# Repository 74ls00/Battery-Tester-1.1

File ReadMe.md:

#### Анализатор батареек и аккумуляторов
----
Анализатор батареек и аккумуляторов разрабатывался по заказу одного из импортёров элементов питания и по мотивам статей для Ф-Центра. Задача — измерение ёмкости и оценка качества батареек в разных режимах разряда, с построением детального графика и сохранением всех полученных данных для демонстрации представителям завода-производителя.

Основные возможности стенда:

- общение с компьютером по USB, полностью программное управление;
- питание от шины USB;
- четыре независимых канала разряда с током 0…3 А каждый и шагом изменения тока 3 мА;
- режимы разряда постоянным током, постоянной мощностью (ток растёт по мере разряда) и на постоянное сопротивление (ток падает по мере разряда);
- режим разряда импульсным током с заданной скважностью;
- любые элементы питания с напряжением до 4,75 В, от батареек до литиевых аккумуляторов;
- 10-битные АЦП и ЦАП;
- индивидуальная калибровка каждого канала по току и напряжению;
- хранение калибровочных параметров в ПЗУ микроконтроллера;
- построение графика напряжения на элементах в реальном времени;
- установка допустимого уровня разряда элементов;
- автоматическое отключение разряженных элементов;
- светодиодная индикация состояния каждого элемента;
- сохранение всех полученных данных в формате CSV;
- автоматический расчёт ёмкости в ампер-часах и ватт-часах, а также внутреннего сопротивления элементов.

Программное обеспечение:

~~[Страница автора](http://olegart.ru/wordpress/batterytester/)~~

[Тема на коте](http://radiokot.ru/forum/viewtopic.php?f=11&t=135313)

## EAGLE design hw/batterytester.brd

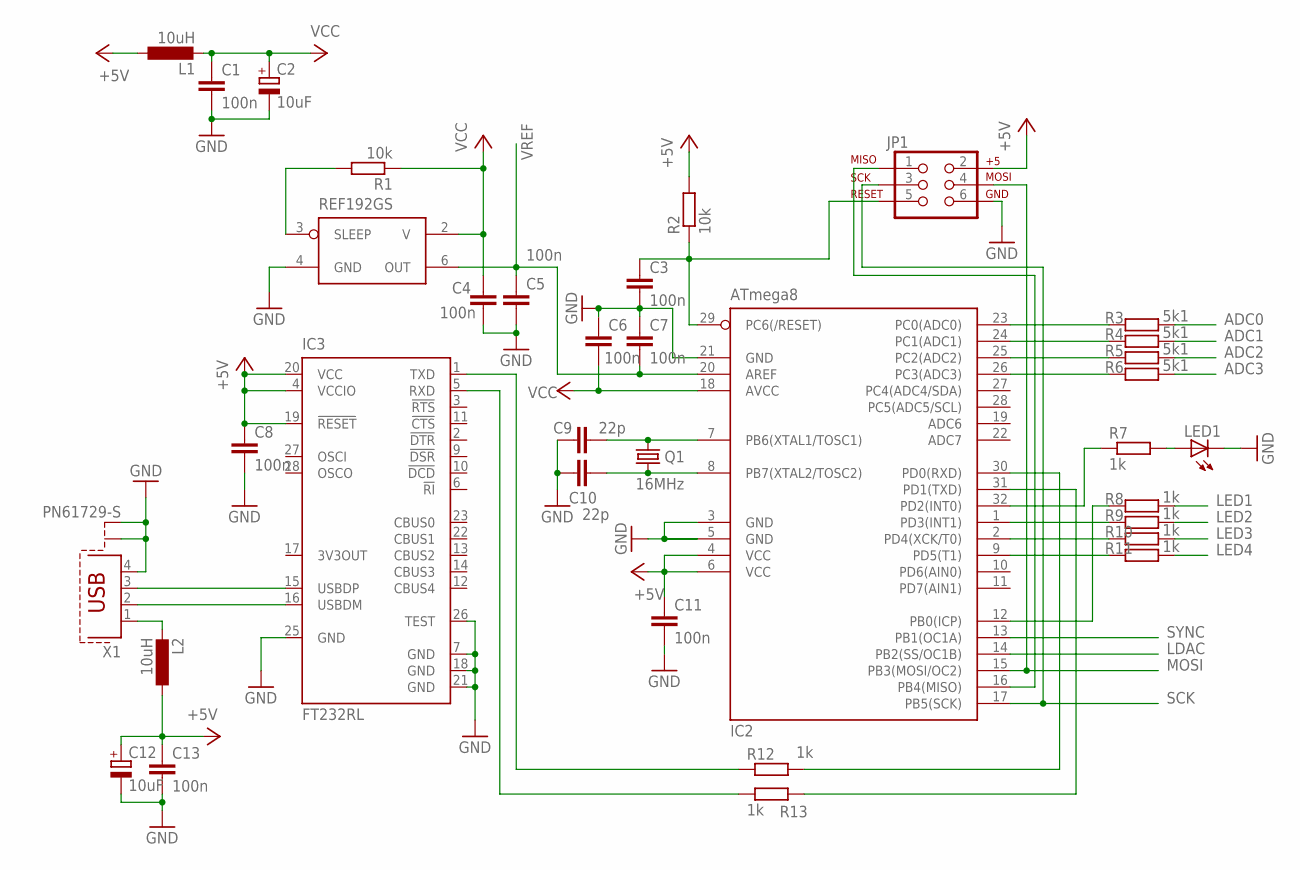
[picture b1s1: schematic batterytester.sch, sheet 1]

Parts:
C1, C3, C4, C5, C6, C7, C8, C11, C13: 100n; C0805
C2, C12: 10uF; SMC_B
C9, C10: 22p; C0805
IC1: REF192GS; SO8
IC2: ATmega8; TQFP32-08
IC3: FT232RL; SSOP28
JP1: AVR_SPI_PRG_6NS; 2X3-NS
L1, L2: 10uH; L1812
LED1: LED3MM
Q1: 16MHz; HC49/S
R1, R2: 10k; R0805
R3, R4, R5, R6: 5k1; R0805
R7, R8, R9, R10, R11, R12, R13: 1k; R0805
X1: PN61729-S

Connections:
+5V: C8.1, C11.1, C12.+, C13.1, IC2.4 (VCC), IC2.6 (VCC), IC3.4 (VCCIO), IC3.19 (!RESET), IC3.20 (VCC), JP1.2, L1.1, L2.1, R2.2; also elsewhere on the board
ADC0: R3.2; also elsewhere on the board
ADC1: R4.2; also elsewhere on the board
ADC2: R5.2; also elsewhere on the board
ADC3: R6.2; also elsewhere on the board
GND: C1.2, C2.-, C3.2, C4.2, C5.2, C6.1, C7.1, C8.2, C9.1, C10.1, C11.2, C12.-, C13.2, IC1.4 (GND), IC2.3 (GND), IC2.5 (GND), IC2.21 (GND), IC3.7 (GND), IC3.18 (GND), IC3.21 (GND), IC3.25 (GND), IC3.26 (TEST), JP1.6, LED1.K (C), X1.4, X1.S1, X1.S2; also elsewhere on the board
LDAC: IC2.14 (PB2(SS/OC1B)); also elsewhere on the board
LED1: R8.2; also elsewhere on the board
LED2: R9.2; also elsewhere on the board
LED3: R10.2; also elsewhere on the board
LED4: R11.2; also elsewhere on the board
MOSI: IC2.15 (PB3(MOSI/OC2)), JP1.4; also elsewhere on the board
unnamed: IC3.1 (TXD), R12.1
unnamed: IC3.5 (RXD), R13.1
unnamed: IC2.30 (PD0(RXD)), R12.2
unnamed: C9.2, IC2.7 (PB6(XTAL1/TOSC1)), Q1.1
unnamed: C10.2, IC2.8 (PB7(XTAL2/TOSC2)), Q1.2
unnamed: IC2.31 (PD1(TXD)), R13.2
unnamed: IC3.16 (USBDM), X1.2
unnamed: IC2.9 (PD5(T1)), R11.1
unnamed: C3.1, IC2.29 (PC6(/RESET)), JP1.5, R2.1
unnamed: IC2.2 (PD4(XCK/T0)), R10.1
unnamed: IC2.12 (PB0(ICP)), R8.1
unnamed: LED1.A, R7.2
unnamed: IC2.32 (PD2(INT0)), R7.1
unnamed: IC2.23 (PC0(ADC0)), R3.1
unnamed: IC3.15 (USBDP), X1.3
unnamed: L2.2, X1.1
unnamed: IC2.16 (PB4(MISO)), JP1.1
unnamed: IC1.3 (SLEEP), R1.2
unnamed: IC2.24 (PC1(ADC1)), R4.1
unnamed: IC2.25 (PC2(ADC2)), R5.1
unnamed: IC2.1 (PD3(INT1)), R9.1
unnamed: IC2.26 (PC3(ADC3)), R6.1
SCK: IC2.17 (PB5(SCK)), JP1.3; also elsewhere on the board
SYNC: IC2.13 (PB1(OC1A)); also elsewhere on the board
VCC: C1.1, C2.+, C4.1, C6.2, IC1.2 (V), IC2.18 (AVCC), L1.2, R1.1; also elsewhere on the board
VREF: C5.1, C7.2, IC1.6 (OUT), IC2.20 (AREF); also elsewhere on the board

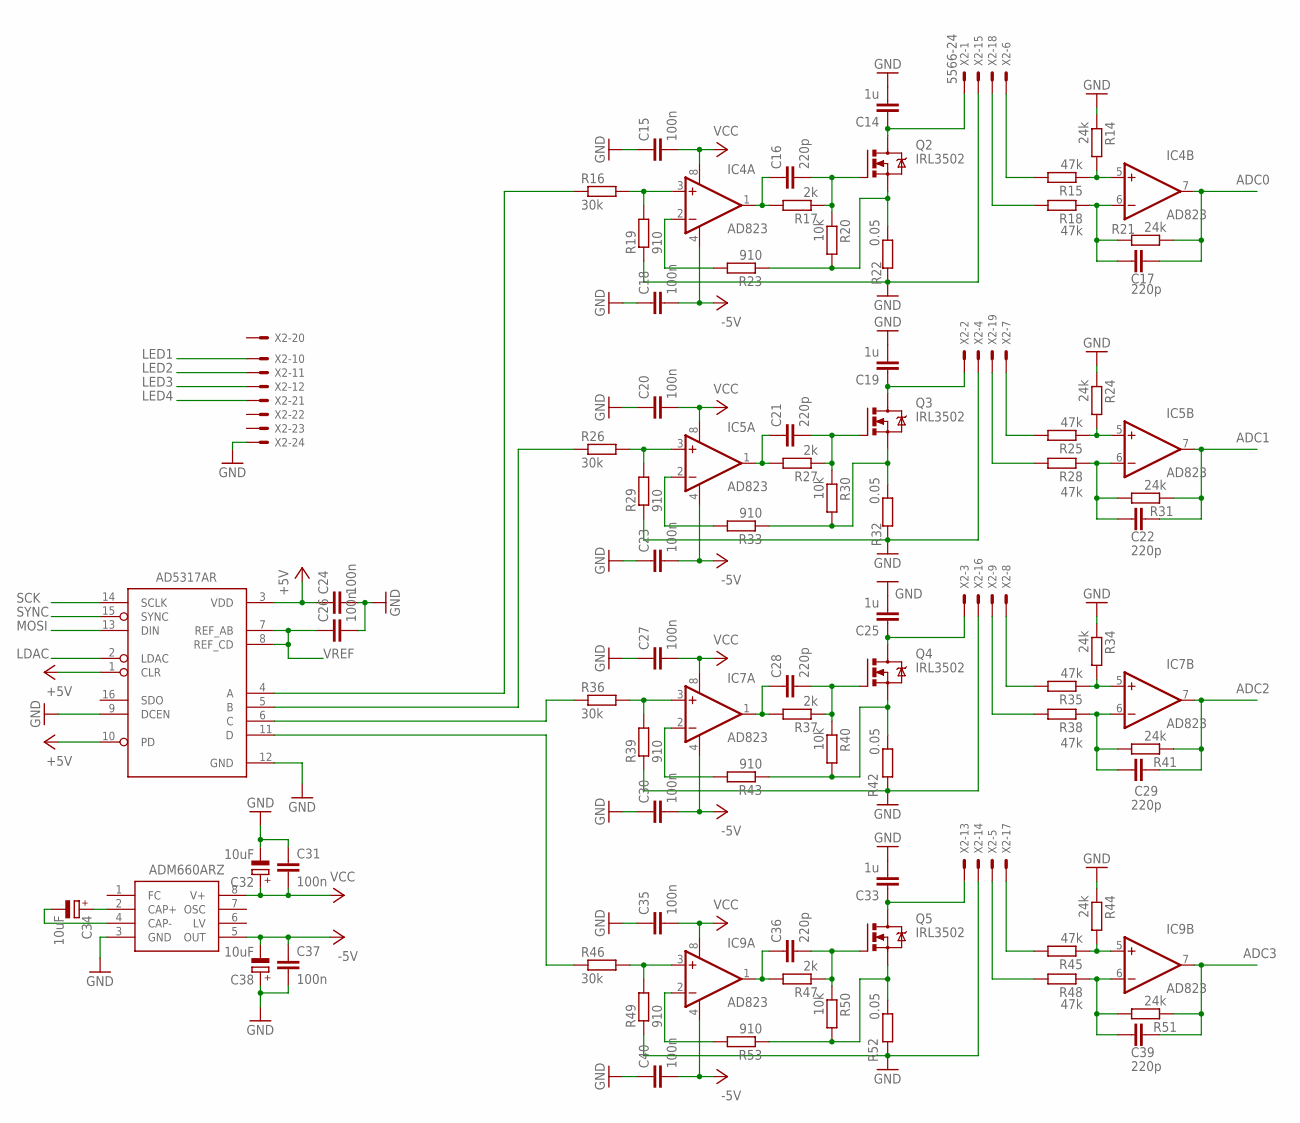
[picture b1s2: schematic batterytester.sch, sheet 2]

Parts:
C14, C19, C25, C33: 1u; C0805
C15, C18, C20, C23, C24, C26, C27, C30, C31, C35, C37, C40: 100n; C0805
C16, C17, C21, C22, C28, C29, C36, C39: 220p; C0805
C32, C34, C38: 10uF; SMC_B
IC4, IC5, IC7, IC9: AD823; SO8
IC6: AD5317AR; TSSOP16
IC8: ADM660ARZ; SO8
Q2, Q3, Q4, Q5: IRL3502; TO220BV
R14, R21, R24, R31, R34, R41, R44, R51: 24k; R0805
R15, R18, R25, R28, R35, R38, R45, R48: 47k; R0805
R16, R26, R36, R46: 30k; R0805
R17, R27, R37, R47: 2k; R0805
R19, R23, R29, R33, R39, R43, R49, R53: 910; R0805
R20, R30, R40, R50: 10k; R0805
R22, R32, R42, R52: 0.05; R2512
X2: 5566-24; 5569-24

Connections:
+5V: C24.1, IC6.1 (CLR), IC6.3 (VDD), IC6.10 (PD); also elsewhere on the board
-5V: C18.2, C23.2, C30.2, C37.1, C38.-, C40.2, IC4.4 (V-), IC5.4 (V-), IC7.4 (V-), IC8.5 (OUT), IC9.4 (V-)
ADC0: C17.2, IC4.7 (OUT), R21.1; also elsewhere on the board
ADC1: C22.2, IC5.7 (OUT), R31.1; also elsewhere on the board
ADC2: C29.2, IC7.7 (OUT), R41.1; also elsewhere on the board
ADC3: C39.2, IC9.7 (OUT), R51.1; also elsewhere on the board
B0: C14.1, Q2.D, X2.1
B0+: R15.2, X2.6
B0-: R18.2, X2.18
B1: C19.1, Q3.D, X2.2
B1+: R25.2, X2.7
B1-: R28.2, X2.19
B2: C25.1, Q4.D, X2.3
B2+: R35.2, X2.8
B2-: R38.2, X2.9
B3: C33.1, Q5.D, X2.13
B3+: R45.2, X2.17
B3-: R48.2, X2.5
GND: C14.2, C15.1, C18.1, C19.2, C20.1, C23.1, C24.2, C25.2, C26.2, C27.1, C30.1, C31.1, C32.-, C33.2, C35.1, C37.2, C38.+, C40.1, IC6.9 (DCEN), IC6.12 (GND), IC8.3 (GND), R14.1, R19.1, R22.2, R24.1, R29.1, R32.2, R34.1, R39.1, R42.2, R44.1, R49.1, R52.2, X2.4, X2.14, X2.15, X2.16, X2.24; also elsewhere on the board
LDAC: IC6.2 (LDAC); also elsewhere on the board
LED1: X2.10; also elsewhere on the board
LED2: X2.11; also elsewhere on the board
LED3: X2.12; also elsewhere on the board
LED4: X2.21; also elsewhere on the board
MOSI: IC6.13 (DIN); also elsewhere on the board
unnamed: IC4.3 (+IN), R16.2, R19.2
unnamed: Q2.S, R20.2, R22.1, R23.1
unnamed: Q3.S, R30.2, R32.1, R33.1
unnamed: C34.+, IC8.2 (CAP+)
unnamed: C34.-, IC8.4 (CAP-)
unnamed: IC4.2 (-IN), R23.2
unnamed: C16.1, IC4.1 (OUT), R17.2
unnamed: C16.2, Q2.G, R17.1, R20.1
unnamed: Q4.S, R40.2, R42.1, R43.1
unnamed: IC4.5 (+IN), R14.2, R15.1
unnamed: C17.1, IC4.6 (-IN), R18.1, R21.2
unnamed: Q5.S, R50.2, R52.1, R53.1
unnamed: IC5.3 (+IN), R26.2, R29.2
unnamed: IC5.2 (-IN), R33.2
unnamed: C21.1, IC5.1 (OUT), R27.2
unnamed: C21.2, Q3.G, R27.1, R30.1
unnamed: IC5.5 (+IN), R24.2, R25.1
unnamed: C22.1, IC5.6 (-IN), R28.1, R31.2
unnamed: IC7.3 (+IN), R36.2, R39.2
unnamed: IC7.2 (-IN), R43.2
unnamed: C28.1, IC7.1 (OUT), R37.2
unnamed: C28.2, Q4.G, R37.1, R40.1
unnamed: IC7.5 (+IN), R34.2, R35.1
unnamed: C29.1, IC7.6 (-IN), R38.1, R41.2
unnamed: IC9.3 (+IN), R46.2, R49.2
unnamed: IC9.2 (-IN), R53.2
unnamed: C36.1, IC9.1 (OUT), R47.2
unnamed: C36.2, Q5.G, R47.1, R50.1
unnamed: IC9.5 (+IN), R44.2, R45.1
unnamed: C39.1, IC9.6 (-IN), R48.1, R51.2
unnamed: IC6.4 (A), R16.1
unnamed: IC6.5 (B), R26.1
unnamed: IC6.6 (C), R36.1
unnamed: IC6.11 (D), R46.1
SCK: IC6.14 (SCLK); also elsewhere on the board
SYNC: IC6.15 (SYNC); also elsewhere on the board
VCC: C15.2, C20.2, C27.2, C31.2, C32.+, C35.2, IC4.8 (V+), IC5.8 (V+), IC7.8 (V+), IC8.8 (V+), IC9.8 (V+); also elsewhere on the board
VREF: C26.1, IC6.7 (REF_AB), IC6.8 (REF_CD); also elsewhere on the board

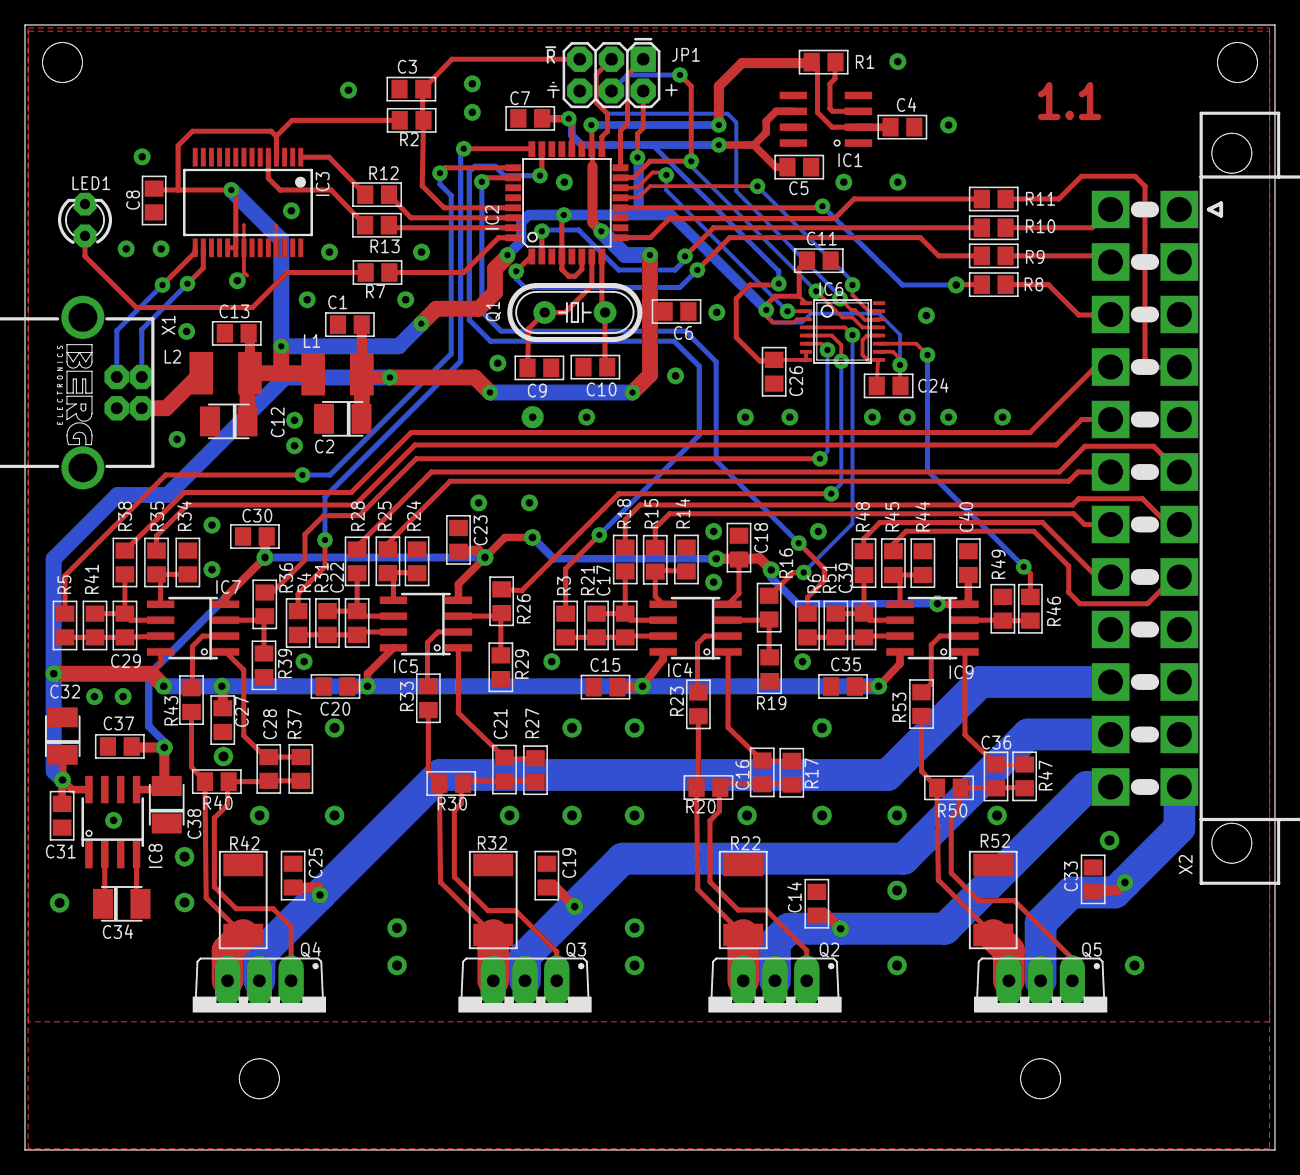
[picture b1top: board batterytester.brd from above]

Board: 2 copper layers, 100.0 x 90.0 mm, 113 parts (0 on the bottom side), 85 nets.

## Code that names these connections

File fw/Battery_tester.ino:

/* Battery tester */
#include <EEPROM.h>
#include <SPI.h>
//#include <MsTimer2.h>
#include <TimedAction.h>

#define MOSI 11
#define SPICLOCK 13
#define LDAC 10
#define SELECT 9

#define LED1 2
#define LED2 8
#define LED3 3
#define LED4 4
#define LED5 5
#define LED6 6
#define LED7 7

int incomingByte = 0;
int analogVal[4];
byte data[34];
unsigned long time;

TimedAction sendData = TimedAction(NO_PREDELAY, 100, ADCout);

void setup()
{  
  analogReference(EXTERNAL);
  Serial.begin(115200);
  
  // LEDs
  pinMode(LED1, OUTPUT);
  pinMode(LED2, OUTPUT);  
  pinMode(LED3, OUTPUT);
  pinMode(LED4, OUTPUT);
  pinMode(LED5, OUTPUT);
  pinMode(LED6, OUTPUT);
  pinMode(LED7, OUTPUT);
  
  // SPI
  pinMode(MOSI, OUTPUT); // MOSI
  pinMode(SPICLOCK, OUTPUT); // Clock
  pinMode(LDAC, OUTPUT); // LDAC
  digitalWrite(LDAC, HIGH);
  pinMode(SELECT, OUTPUT); // Select
  digitalWrite(SELECT, HIGH);
  SPI.mode(1 << CPHA); // send SPI data on the falling edge of SCLK
  delay(10);
  for (int i=0; i<4; i++) // write zeros to DAC
  {
    digitalWrite(SELECT, LOW); // enable DAC input register
    Spi.transfer((char)(i<<6)); // send MSB
    Spi.transfer(0);
    digitalWrite(SELECT, HIGH); // disable DAC input register    
  }
  digitalWrite(LDAC, LOW); // update DAC outputs
  delay(1); // 1 ms delay
  digitalWrite(LDAC, HIGH); // release LDAC
  
  // Timer
  // MsTimer2::set(100, ADCout); // every 100 ms
  sendData.disable();
  
  for (int l=0; l<3; l++)
  {
    digitalWrite(LED1, HIGH);
    delay(100);
    digitalWrite(LED1, LOW);
    digitalWrite(LED2, HIGH);
    delay(100);
    digitalWrite(LED2, LOW);
    digitalWrite(LED3, HIGH);
    delay(100);
    digitalWrite(LED3, LOW);
    digitalWrite(LED4, HIGH);
    delay(100);
    digitalWrite(LED4, LOW);
    digitalWrite(LED5, HIGH);
    delay(100);
    digitalWrite(LED5, LOW);
    digitalWrite(LED6, HIGH);
    delay(100);
    digitalWrite(LED6, LOW);
    digitalWrite(LED7, HIGH);
    delay(100);
    digitalWrite(LED7, LOW);
  }
}

void loop()
{
  if (Serial.available() > 1)
  {
    incomingByte = Serial.read();
    if (incomingByte == 0x55)
    {
      incomingByte = Serial.read();
      if (incomingByte == 0xAA)      
      {
        do
        {
          delayMicroseconds(1);
        }
        while (Serial.available() == 0);
        incomingByte = Serial.read();
        switch(incomingByte)
        {
        case 0x30:  // read voltages
          ADCout(); 
          break;
        case 0x31:
          setCurrent(); // set current
          break;
        case 0x32:
          setLEDs(); // enable/disable LED1...LED7
          break;
        case 0x33:  // start auto-measurements every 100 ms
          time = millis();
          sendData.enable();
          break;
        case 0x34:  // stop auto-measurements
          sendData.disable();
          break;
        case 0x40: 
          EEPROMread(); // read EEPROM
          break;
        case 0x41: 
          EEPROMwrite();  //write EEPROM
          break;
        }
      }
    }
  }
  // send ADC data every 100 ms
  sendData.check();
}

void ADCout()
{
  unsigned short i;
  for (i=0; i<4; i++)
  {
    analogVal[i] = 0;   
  } 
  for (unsigned short j=0; j<4; j++)
  { 
    for (i=0; i<4; i++)
    {
      analogVal[j] += analogRead(j);   
    }
    analogVal[j] >>= 2;
  }  
  
  Serial.print(0x55, BYTE);
  unsigned long ctime;
  ctime = millis() - time;
  for (i=0; i<4; i++)
  {
      Serial.write(lowByte(ctime));
      ctime >>= 8;
  }
  for (i=0; i<4; i++)
  {
    Serial.write(lowByte(analogVal[i]));    
    Serial.write(highByte(analogVal[i]));    
  }
}

void EEPROMread()
{
  Serial.write(0x55);
  // 1st & 2nd bytes - firmware version
  // 4 bytes - float
  // 4 channels, voltage and current, 12 bytes each channel
  // 2 + 12*4  = 50 bytes total (BLOCKSIZE)
  for (int i=0; i<50; i++)
  {
    Serial.write(EEPROM.read(i));
  }
}

void EEPROMwrite()
{
  int i = 0;
  int j = 0;
  do
  {
    if (Serial.available() > 0)
    {
      data[i] = Serial.read();
      i++;
    }
    delayMicroseconds(10);
    j++;
    if (j>10000) // 100 ms
    {
      // timeout
      Serial.write(0x31);
      return;
    }
  }
  while (i<50);
  // write received bytes to the EEPROM
  for (int j=0; j<50; j++)
  {
    EEPROM.write(j, data[j]);
  }
}

void setCurrent(void)
{
  byte i=0;
  int j=0;
  do
  {
    if (Serial.available() > 0)
    {
      data[i] = Serial.read();
      i++;
    }
    delayMicroseconds(1);
    j++;
    if (j>10000) // 10 ms timeout
    {
      return;
    }
  }
  while (i<8); // 4 channels * 2 bytes each
  
  for (i=0; i<4; i++)
  {
    data[2*i+1] += (char)(i<<6); // DAC output address - first (most significant) two bits
    digitalWrite(SELECT, LOW); // enable DAC input register
    Spi.transfer(data[2*i+1]); // send MSB
    Spi.transfer(data[2*i]); // send LSB
    digitalWrite(SELECT, HIGH); // disable DAC input register
    delayMicroseconds(100);
  }
  digitalWrite(LDAC, LOW); // update DAC outputs
  delay(1); // 1 ms delay
  digitalWrite(LDAC, HIGH); // release LDAC
}

void setLEDs(void)
{
  byte leds;
  int i=0;
  int j=0;
  do
  {
    if (Serial.available() > 0)
    {
      leds = Serial.read();
      break;
    }
    delayMicroseconds(10);
    j++;
    if (j>1000) // 10 ms
    {
      // timeout
      return;
    }
  }
  while (true); // 1 byte
  // enable/disable status LEDs
  digitalWrite(LED7, bitRead(leds, 6));
  digitalWrite(LED6, bitRead(leds, 5));
  digitalWrite(LED5, bitRead(leds, 4));
  digitalWrite(LED4, bitRead(leds, 3));
  digitalWrite(LED3, bitRead(leds, 2));
  digitalWrite(LED2, bitRead(leds, 1));
  digitalWrite(LED1, bitRead(leds, 0));
}

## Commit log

2016-09-09 add pcb lay6
2016-09-10 add png
